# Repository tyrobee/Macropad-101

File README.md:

# Macropad-101
# 9-Key Macropad 

This is my custom 9-key macropad project.  

##V1(Wired)

I designed the PCB in KiCad, created a simple case in Fusion 360 ,  
and wrote the firmware using KMK on a Seeed XIAO RP2040.
Even though this is my first time doing PCB and CAD together, I wanted some background lighting so I added RGB on the back of the pcb.

##V2(Wireless)

I designed the PCB in KiCad, created a simple case in Fusion 360 ,  
and wrote the firmware using KMK on a Seeed XIAO nRF52840 which make it compeletly wireless while the v1 need to be connected to the pc all the time.

---

##  Project Photos

### PCB Layout (V1)

### PCB Layout (V2)

### Schematic (V1)

### Schematic (V2)

### Assembled Board 

### Case (Fusion 360)  

## Why These 9 Shortcuts?

I wanted shortcuts that I use constantly, either for coding or just daily use.
Here’s the logic behind each row:

###  **Top Row – Audio Controls**
1. **Volume Down** – quick sound adjustment  
2. **Mute** – useful during calls or when someone walks in  
3. **Volume Up** – because everything is too quiet sometimes  

These three are simple, universal, and felt right as the “top bar.”

---

### **Middle Row**
4. **Open Terminal** – I open terminal windows constantly  
5. **Open YouTube** – background videos/music while I work  
6. **Open VS Code** – my main coding environment  

These shortcuts save me a ton of time. Instead of searching or alt-tabbing,
I can just tap a key.

---

###  **Bottom Row**
7. **Screenshot** – I take screenshots very often (errors, memes, notes)  
8. **VS Code Terminal Toggle** – I switch terminals repeatedly while coding  
9. **Open KiCad** – since I'm always tweaking my PCB design, having this shortcut made sense  

I chose shortcuts based on what I genuinely use dozens of times a day.  
This macropad ended up improving my workflow more than I expected.

---

## RGB Lighting

I added two SK6812 RGB LEDs for the background lighting and the gamer vibe
---

##  Case Design
I used fusion 360 for the design of the case which was hell lotta fun ngl
---

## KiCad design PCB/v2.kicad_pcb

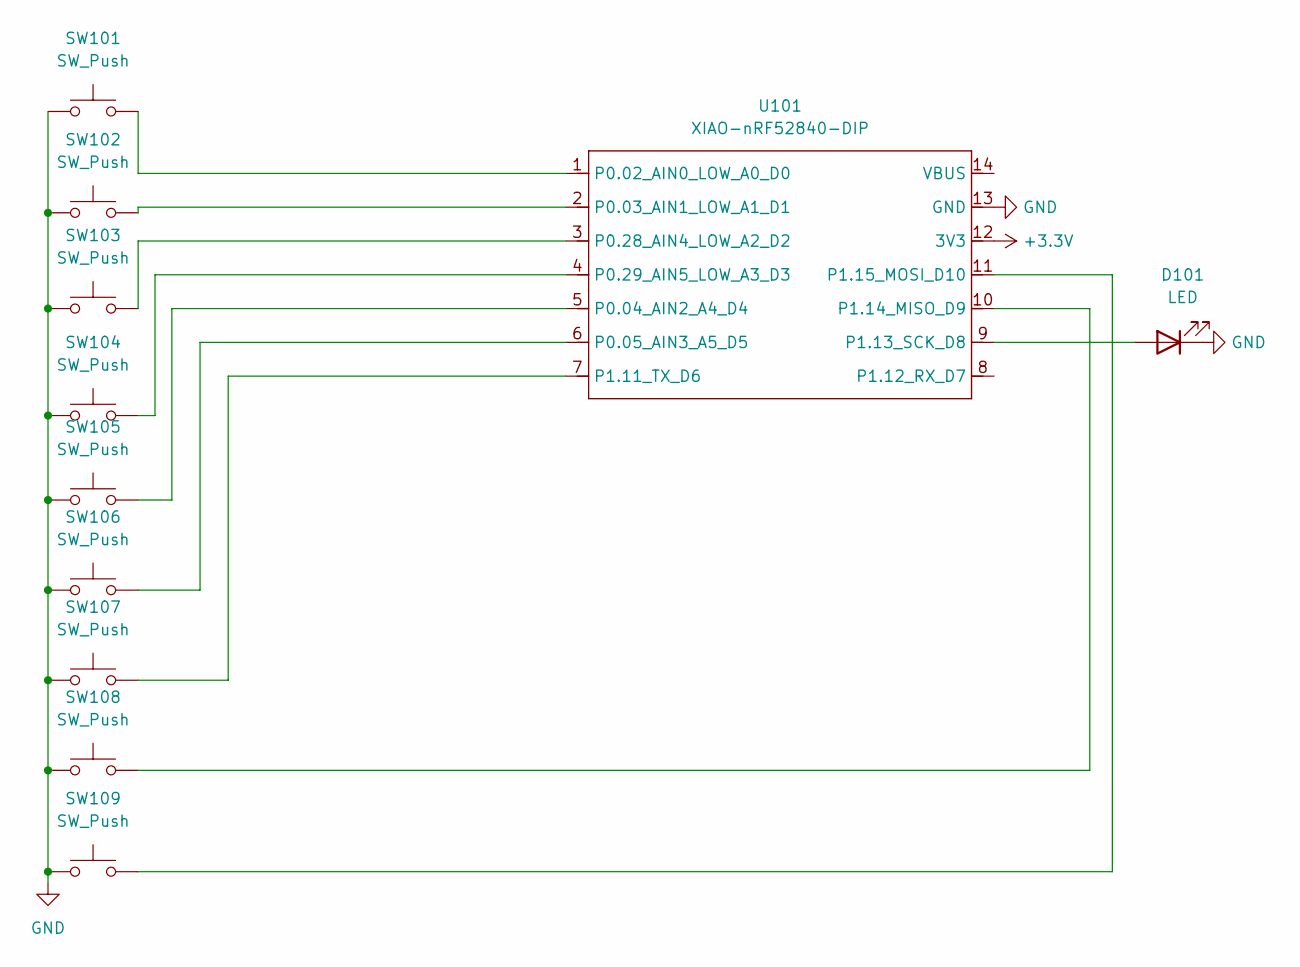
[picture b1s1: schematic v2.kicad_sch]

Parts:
D101: LED; LED_D5.0mm
SW101, SW102, SW103, SW104, SW105, SW106, SW107, SW108, SW109: SW_Push; SW_Cherry_MX_1.00u_PCB
U101: XIAO-nRF52840-DIP; MCU_Seeed_ESP32C3

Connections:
+3.3V: U101.12 (3V3)
GND: D101.1 (K), SW101.1, SW102.1, SW103.1, SW104.1, SW105.1, SW106.1, SW107.1, SW108.1, SW109.1, U101.13 (GND)
unnamed: D101.2 (A), U101.9 (P1.13_SCK_D8)
unnamed: SW101.2, U101.1 (P0.02_AIN0_LOW_A0_D0)
unnamed: SW102.2, U101.2 (P0.03_AIN1_LOW_A1_D1)
unnamed: SW105.2, U101.5 (P0.04_AIN2_A4_D4)
unnamed: SW106.2, U101.6 (P0.05_AIN3_A5_D5)
unnamed: SW103.2, U101.3 (P0.28_AIN4_LOW_A2_D2)
unnamed: SW104.2, U101.4 (P0.29_AIN5_LOW_A3_D3)
unnamed: SW107.2, U101.7 (P1.11_TX_D6)
unnamed: SW108.2, U101.10 (P1.14_MISO_D9)
unnamed: SW109.2, U101.11 (P1.15_MOSI_D10)

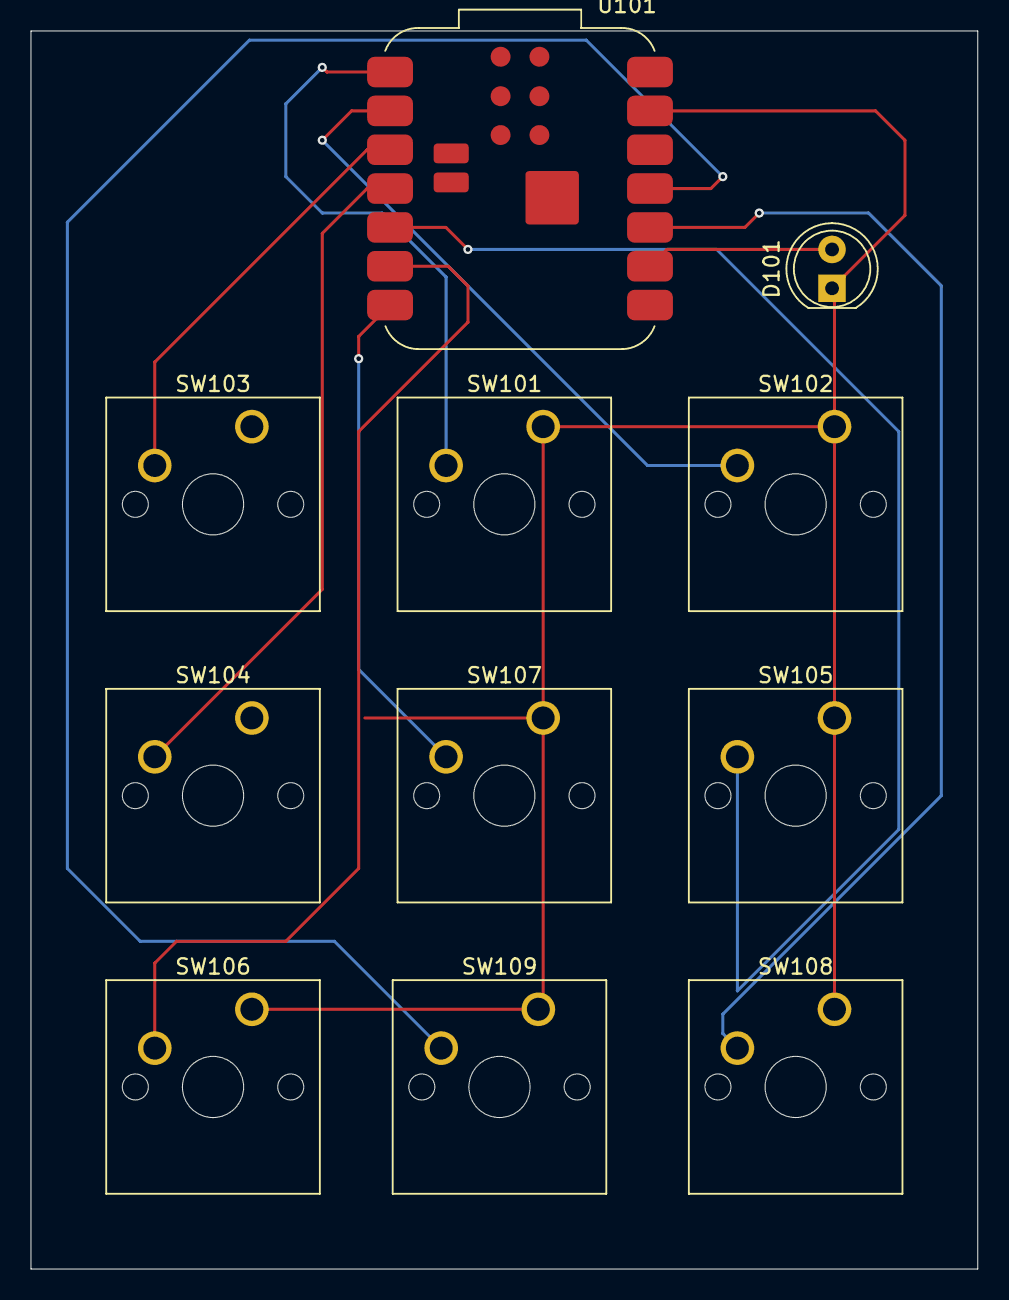
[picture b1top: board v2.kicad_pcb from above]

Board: 2 copper layers, 61.9 x 81.0 mm, 11 parts (0 on the bottom side), 11 nets.

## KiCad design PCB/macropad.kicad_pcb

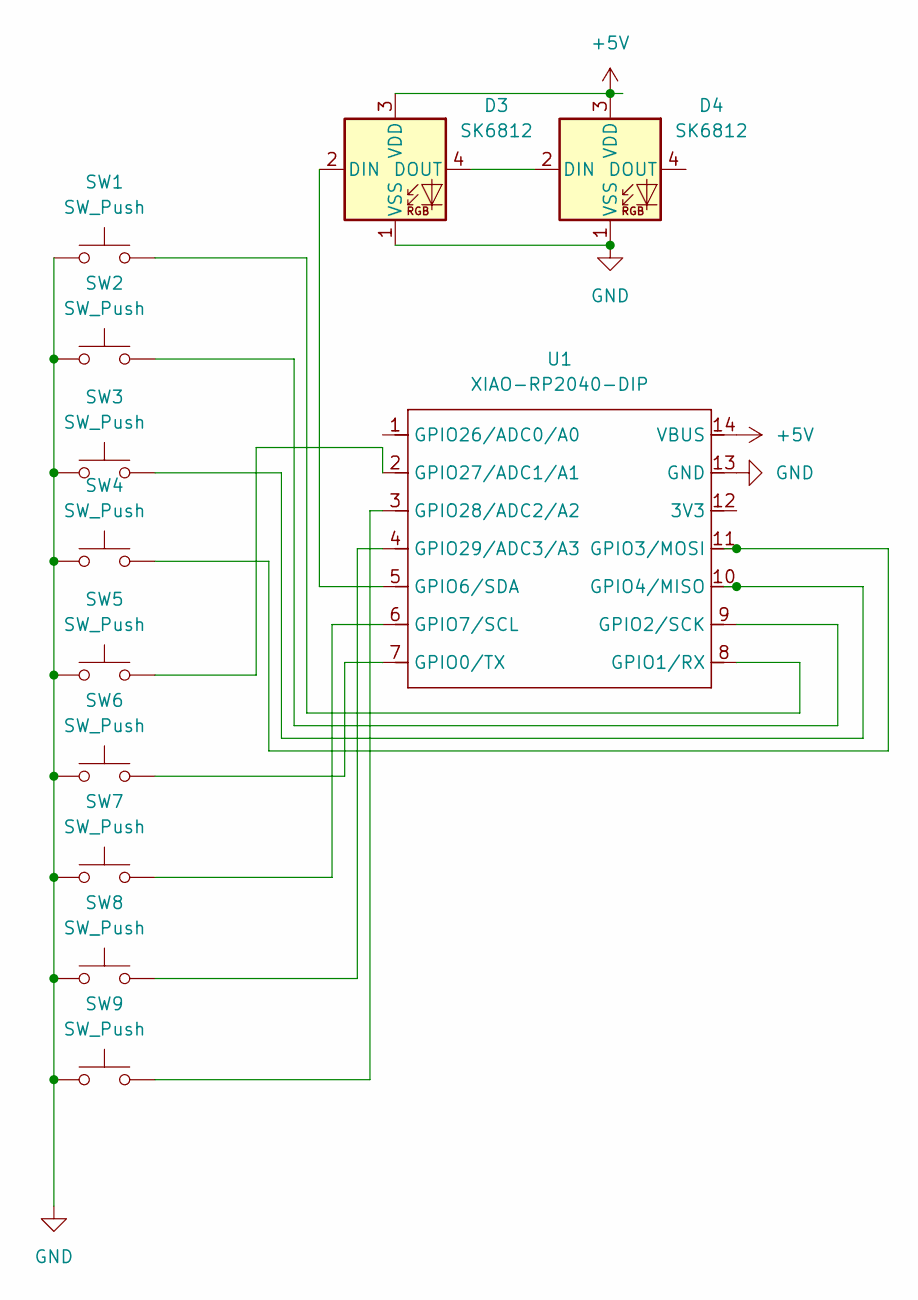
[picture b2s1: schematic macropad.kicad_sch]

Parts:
D3, D4: SK6812; LED_SK6812MINI_PLCC4_3.5x3.5mm_P1.75mm
SW1, SW2, SW3, SW4, SW5, SW6, SW7, SW8, SW9: SW_Push; SW_Cherry_MX_1.00u_PCB
U1: XIAO-RP2040-DIP

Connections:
+5V: D3.3 (VDD), D4.3 (VDD), U1.14 (VBUS)
GND: D3.1 (VSS), D4.1 (VSS), SW1.1, SW2.1, SW3.1, SW4.1, SW5.1, SW6.1, SW7.1, SW8.1, SW9.1, U1.13 (GND)
unnamed: D3.2 (DIN), U1.5 (GPIO6/SDA)
unnamed: D3.4 (DOUT), D4.2 (DIN)
unnamed: SW6.2, U1.7 (GPIO0/TX)
unnamed: SW1.2, U1.8 (GPIO1/RX)
unnamed: SW2.2, U1.9 (GPIO2/SCK)
unnamed: SW4.2, U1.11 (GPIO3/MOSI)
unnamed: SW3.2, U1.10 (GPIO4/MISO)
unnamed: SW7.2, U1.6 (GPIO7/SCL)
unnamed: SW5.2, U1.2 (GPIO27/ADC1/A1)
unnamed: SW9.2, U1.3 (GPIO28/ADC2/A2)
unnamed: SW8.2, U1.4 (GPIO29/ADC3/A3)

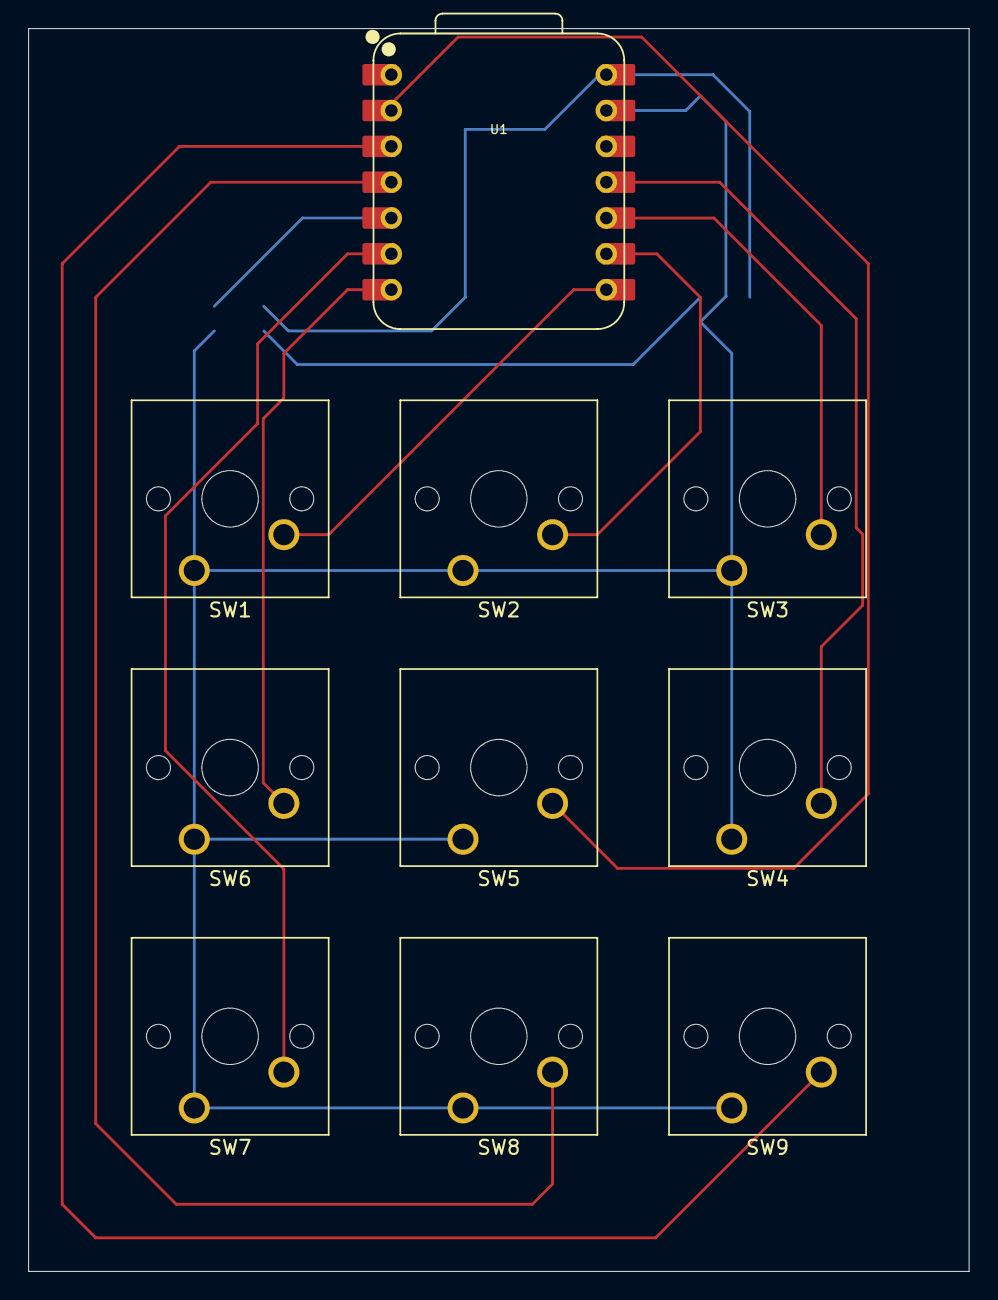
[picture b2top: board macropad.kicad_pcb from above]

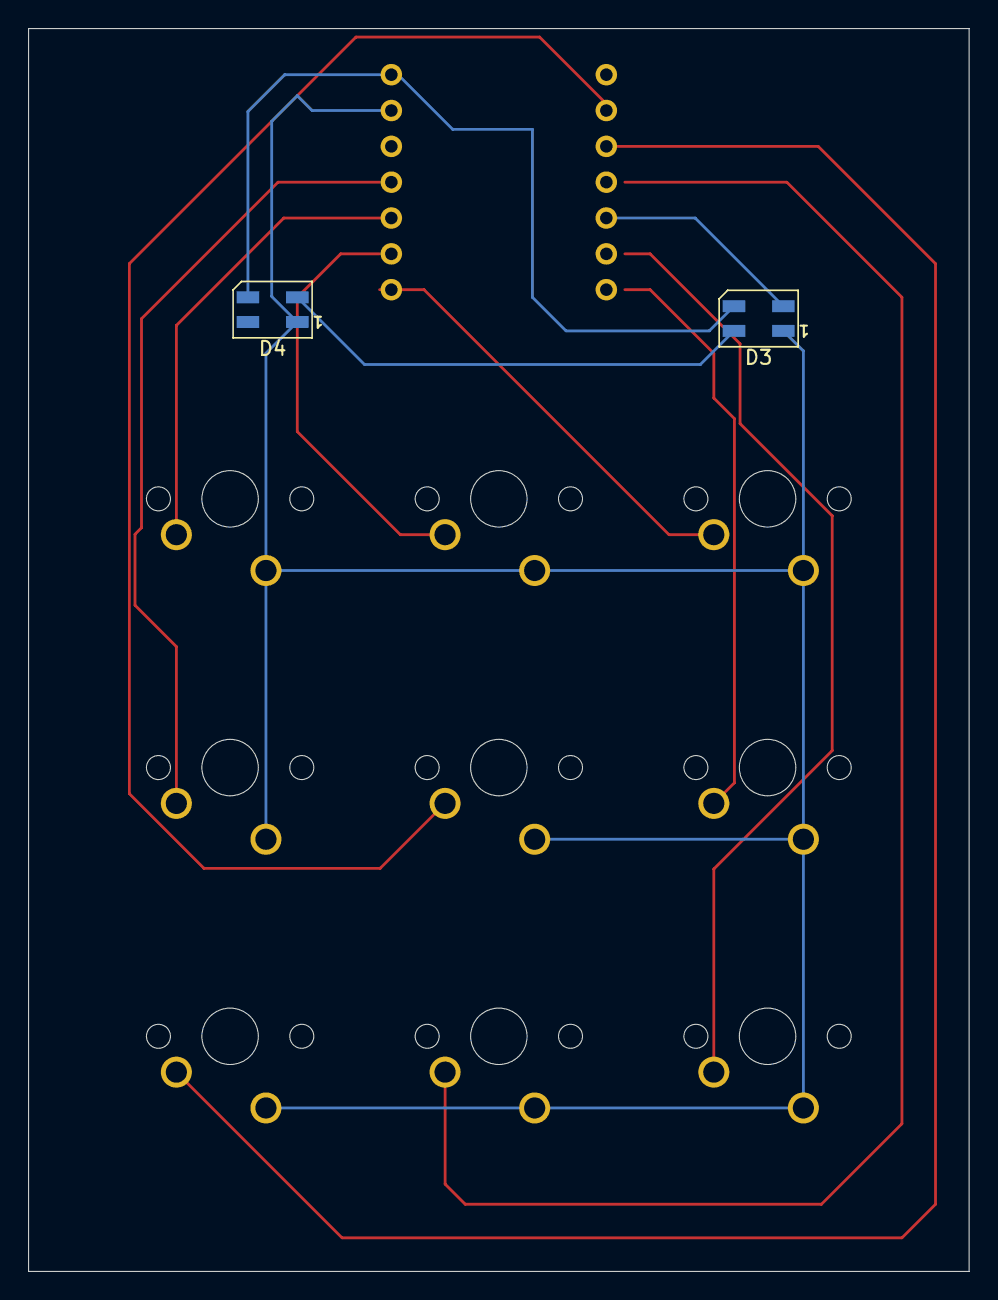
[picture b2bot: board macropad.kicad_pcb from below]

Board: 2 copper layers, 66.7 x 88.1 mm, 12 parts (2 on the bottom side), 13 nets.

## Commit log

2025-12-05 Added files
2025-12-05 photos
2025-12-05 Add README
2025-12-11 newbom
2026-03-25 Update README with V2 details and images
    Added details for V2 of the macropad, including design and features.
2026-03-25 Update README for board and BOM image sections
2026-03-25 Fix image file names in README
    Updated image file names in README for consistency.
2026-03-25 Rename c v2.png to c_v2.png
2026-03-25 Rename p v2.png to -pv2.png
2026-03-25 Rename -pv2.png to p_v2.png
2026-03-25 Change section headers for V1 and V2
    Updated section headers for V1 and V2 in README.md.
2026-03-25 Delete BOM image section
    Removed BOM image section from README.
